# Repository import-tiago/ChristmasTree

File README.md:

# ChristmasTree

## PCB Preview

## Schematic

## Bill of Materials
| Qty | Parts | Description | Value | Package |
|--|--|--|--|--|
1|R1|SMD Resistor|10k ±5%|R0603
2|R2/R3|SMD Resistor|22R ±5%|R0603
1|R4|SMD Resistor|150R ±5%|R0603
1|R5|SMD Resistor|220k ±5%|R0603
1|C1|SMD Capacitor|1uF / 50V|C0805
1|C2|SMD Capacitor|10nF / 50V|C0603
2|C3/C5|SMD Capacitor|1uF / 50V|C0603
17|C4/C6~C21|SMD Capacitor|100nF / 50V|C0603
1|LDR1|PTH LDR|1 MΩ (Lux 0) / 10-20 KΩ (Lux 10)|5mm
1|Y1|SMD Crystal|8MHz|5.0mm x 3.2mm
1|U1|SMD Integrated Circuit|RT9193-33GB|SOT23-5
1|U2|SMD Integrated Circuit|ATMEGA32U4|QFN-44
2|D1/D2|SMD Diode|SS34|DO214AB
1|CN1|SMD Connector|MISB-SW-5B|Micro USB Type B
1|CN2|PTH Connector|JST-PH-2P|2-pin
13|LED1~LED13|SMD RGB LED|WS2812B|5050

### Contributing
0. Give this project a :star:
1. Create an issue and describe your idea.
2. [Fork it](https://github.com/import-tiago/ChristmasTree/fork).
3. Create your feature branch (`git checkout -b my-new-feature`).
4. Commit your changes (`git commit -a -m "Added feature title"`).
5. Publish the branch (`git push origin my-new-feature`).
6. Create a new pull request.
7. Done! :heavy_check_mark:

### License Information
<br /><span xmlns:dct="http://purl.org/dc/terms/" property="dct:title">ChristmasTree</span> by <a xmlns:cc="http://creativecommons.org/ns#" href="https://github.com/import-tiago" property="cc:attributionName" rel="cc:attributionURL">Tiago Silva</a> is licensed under a <a rel="license" href="http://creativecommons.org/licenses/by-sa/4.0/">Creative Commons Attribution-ShareAlike 4.0 International License</a>.<br />Permissions beyond the scope of this license may be available at <a xmlns:cc="http://creativecommons.org/ns#" href="https://twitter.com/import_tiago" rel="cc:morePermissions">tiagodepaulasilva@gmail.com</a>.

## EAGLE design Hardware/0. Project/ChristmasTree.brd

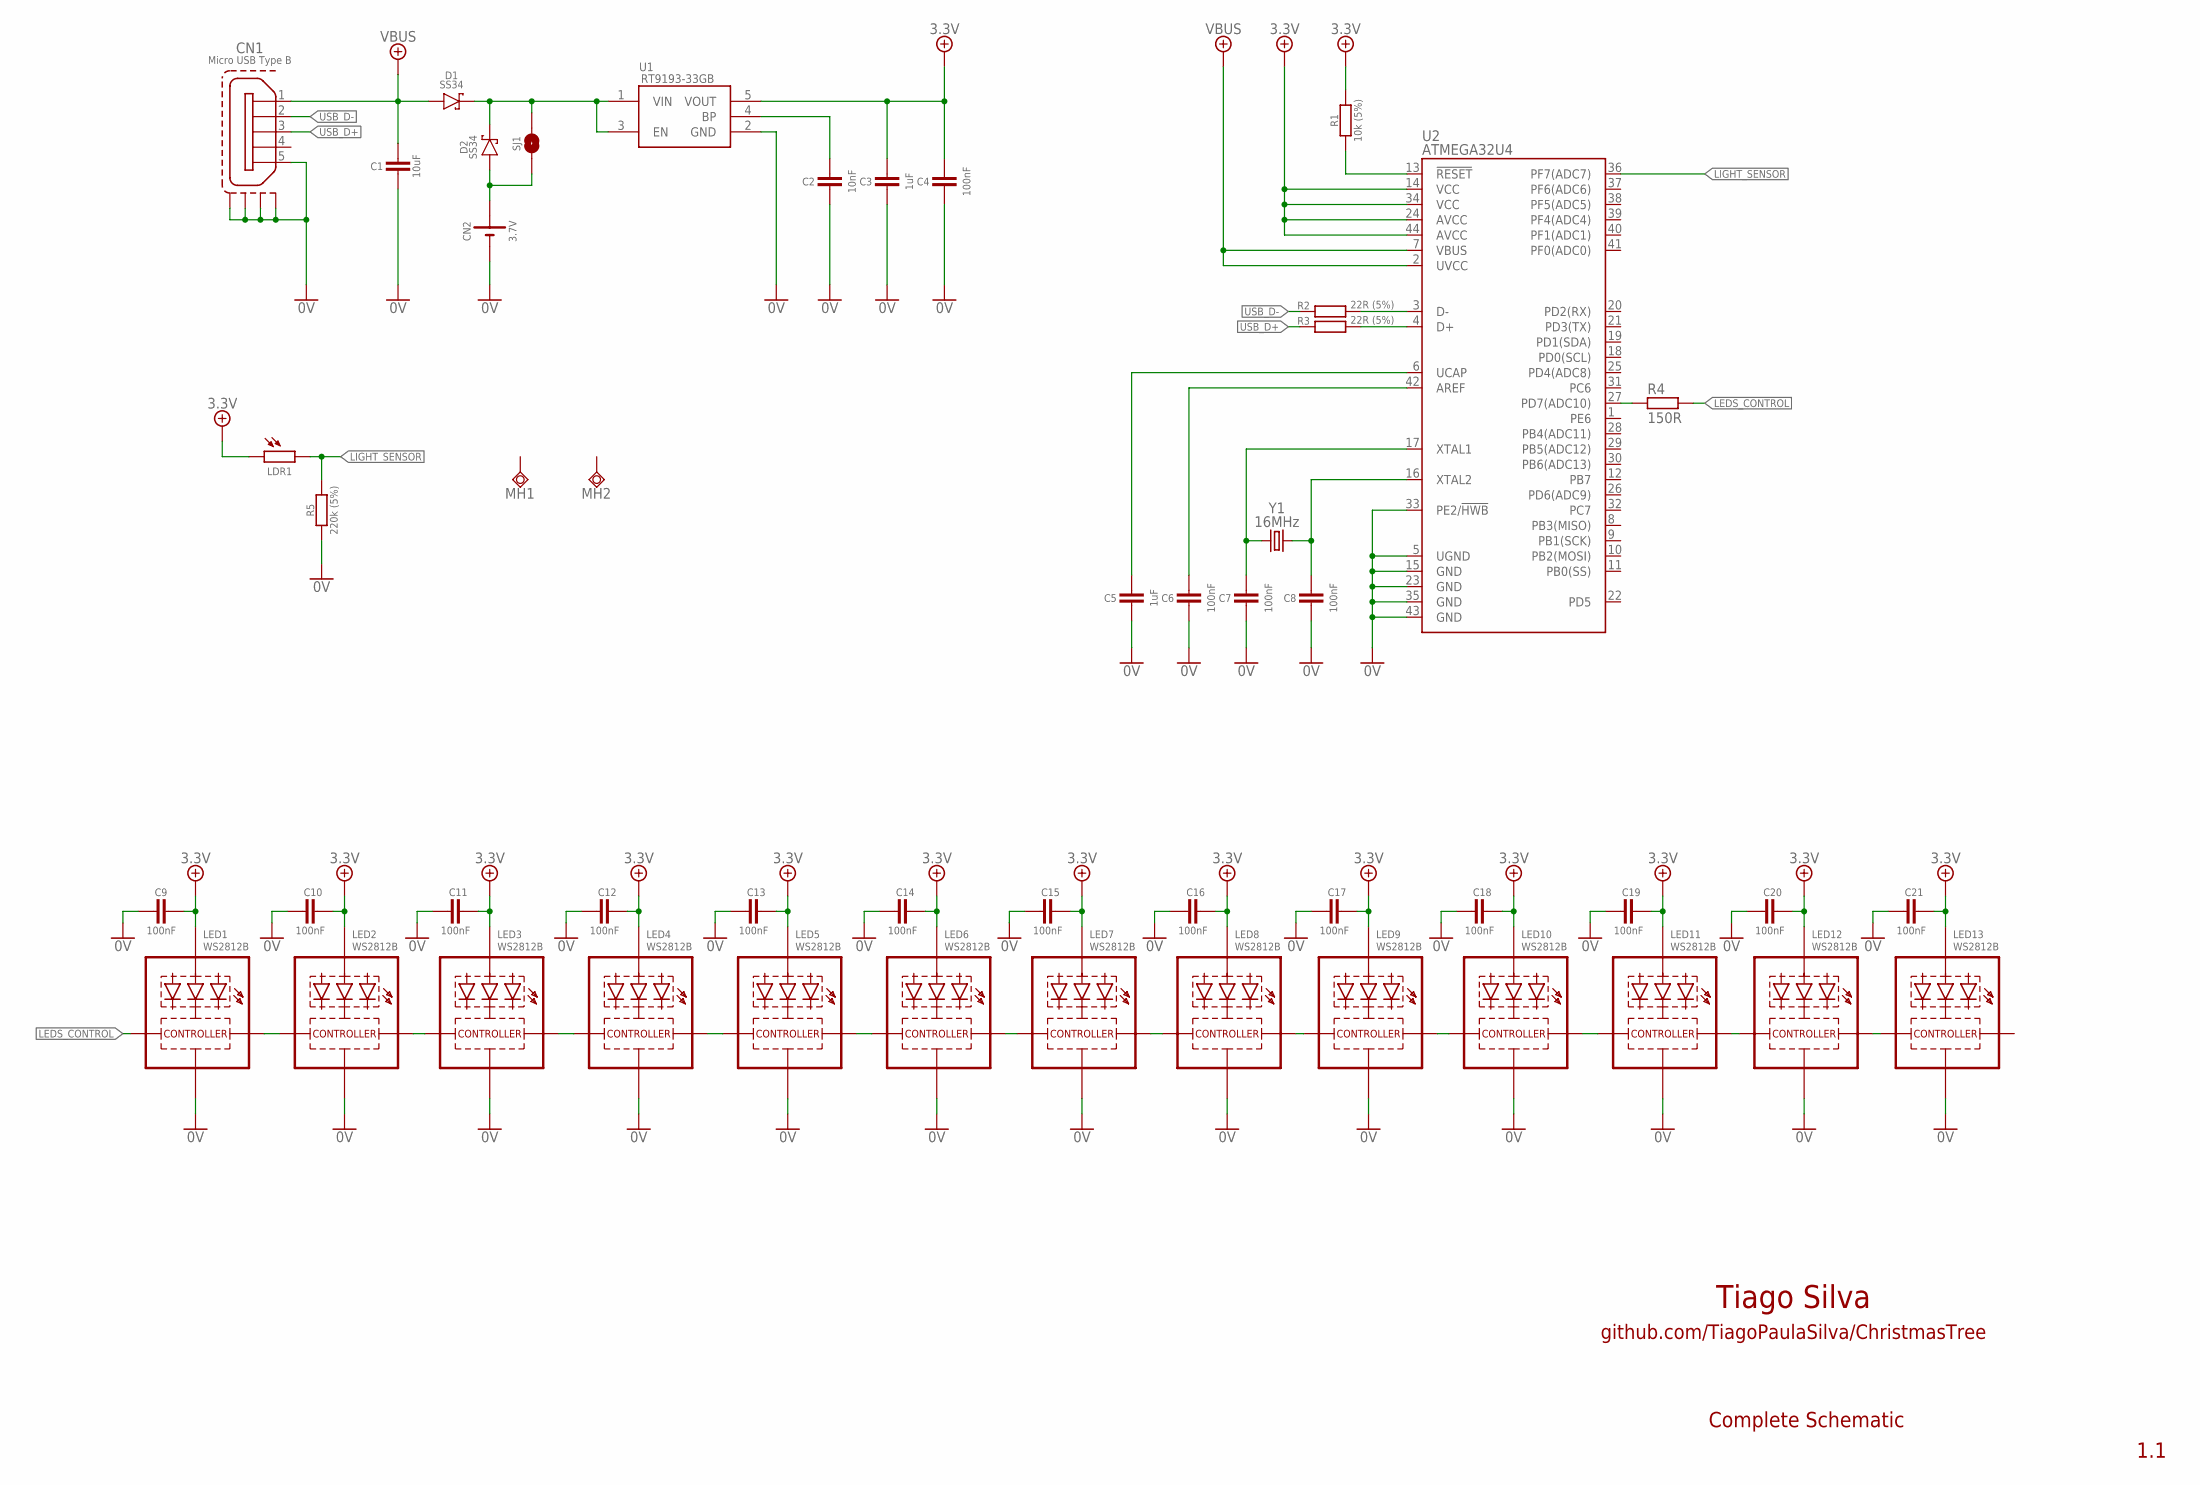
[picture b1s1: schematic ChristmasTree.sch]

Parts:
C1: 10uF; C0805
C2: 10nF; C0603
C3, C5: 1uF; C0603
C4, C6, C7, C8, C9, C10, C11, C12, C13, C14, C15, C16, C17, C18, C19, C20, C21: 100nF; C0603
CN1: Micro USB Type B; 10118193-0001LF
CN2: 3.7V; JST-PH2
D1, D2: SS34; DO214AB
LDR1: A1050_09; T0-46-A10XX
LED1, LED2, LED3, LED4, LED5, LED6, LED7, LED8, LED9, LED10, LED11, LED12, LED13: WS2812B; 5050
MH1, MH2: TPSQTP20R; TP20R
R1: 10k (5%); R0603
R2, R3: 22R (5%); R0603
R4: 150R; R0603
R5: 220k (5%); R0603
SJ1: SJ
U1: RT9193-33GB; SOT94P279X129-5N
U2: ATMEGA32U4; TESTING_QFN-44
Y1: 16MHz; 5.0X3.2_KX-9A

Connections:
0V: C1.2, C2.2, C3.2, C4.2, C5.2, C6.2, C7.2, C8.2, C9.2, C10.2, C11.2, C12.2, C13.2, C14.2, C15.2, C16.2, C17.2, C18.2, C19.2, C20.2, C21.2, CN1.5, CN1.MP1 (S1), CN1.MP2 (S2), CN1.MP3 (S3), CN1.MP4 (S4), CN2.2 (-), LED1.3-GND (GND), LED2.3-GND (GND), LED3.3-GND (GND), LED4.3-GND (GND), LED5.3-GND (GND), LED6.3-GND (GND), LED7.3-GND (GND), LED8.3-GND (GND), LED9.3-GND (GND), LED10.3-GND (GND), LED11.3-GND (GND), LED12.3-GND (GND), LED13.3-GND (GND), R5.1, U1.2 (GND), U2.5 (UGND), U2.15 (GND), U2.23 (GND), U2.33 (PE2/!HWB), U2.35 (GND), U2.43 (GND)
3.3V: C3.1, C4.1, C9.1, C10.1, C11.1, C12.1, C13.1, C14.1, C15.1, C16.1, C17.1, C18.1, C19.1, C20.1, C21.1, LDR1.1, LED1.1-VDD (VDD), LED2.1-VDD (VDD), LED3.1-VDD (VDD), LED4.1-VDD (VDD), LED5.1-VDD (VDD), LED6.1-VDD (VDD), LED7.1-VDD (VDD), LED8.1-VDD (VDD), LED9.1-VDD (VDD), LED10.1-VDD (VDD), LED11.1-VDD (VDD), LED12.1-VDD (VDD), LED13.1-VDD (VDD), R1.2, U1.5 (VOUT), U2.14 (VCC), U2.24 (AVCC), U2.34 (VCC), U2.44 (AVCC)
LEDS_CONTROL: LED1.4-DIN (DI), R4.2
LIGHT_SENSOR: LDR1.2, R5.2, U2.36 (PF7(ADC7))
unnamed: LED3.2-DOUT (DO), LED4.4-DIN (DI)
unnamed: LED1.2-DOUT (DO), LED2.4-DIN (DI)
unnamed: R4.1, U2.27 (PD7(ADC10))
unnamed: LED2.2-DOUT (DO), LED3.4-DIN (DI)
unnamed: LED5.2-DOUT (DO), LED6.4-DIN (DI)
unnamed: LED8.2-DOUT (DO), LED9.4-DIN (DI)
unnamed: LED6.2-DOUT (DO), LED7.4-DIN (DI)
unnamed: LED10.2-DOUT (DO), LED11.4-DIN (DI)
unnamed: LED9.2-DOUT (DO), LED10.4-DIN (DI)
unnamed: LED12.2-DOUT (DO), LED13.4-DIN (DI)
unnamed: LED4.2-DOUT (DO), LED5.4-DIN (DI)
unnamed: R3.2, U2.4 (D+)
unnamed: LED11.2-DOUT (DO), LED12.4-DIN (DI)
unnamed: LED7.2-DOUT (DO), LED8.4-DIN (DI)
unnamed: C7.1, U2.17 (XTAL1), Y1.1
unnamed: C8.1, U2.16 (XTAL2), Y1.3 (2)
unnamed: C5.1, U2.6 (UCAP)
unnamed: C6.1, U2.42 (AREF)
unnamed: CN2.1 (+), D2.A, SJ1.1
unnamed: R2.2, U2.3 (D-)
unnamed: C2.1, U1.4 (BP)
RESET: R1.1, U2.13 (!RESET)
USB_D+: CN1.3, R3.1
USB_D-: CN1.2, R2.1
VBAT: D1.C (K), D2.C (K), SJ1.2, U1.1 (VIN), U1.3 (EN)
VBUS: C1.1, CN1.1, D1.A, U2.2 (UVCC), U2.7 (VBUS)

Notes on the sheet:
Tiago Silva
github.com/TiagoPaulaSilva/ChristmasTree
1.1
Complete Schematic

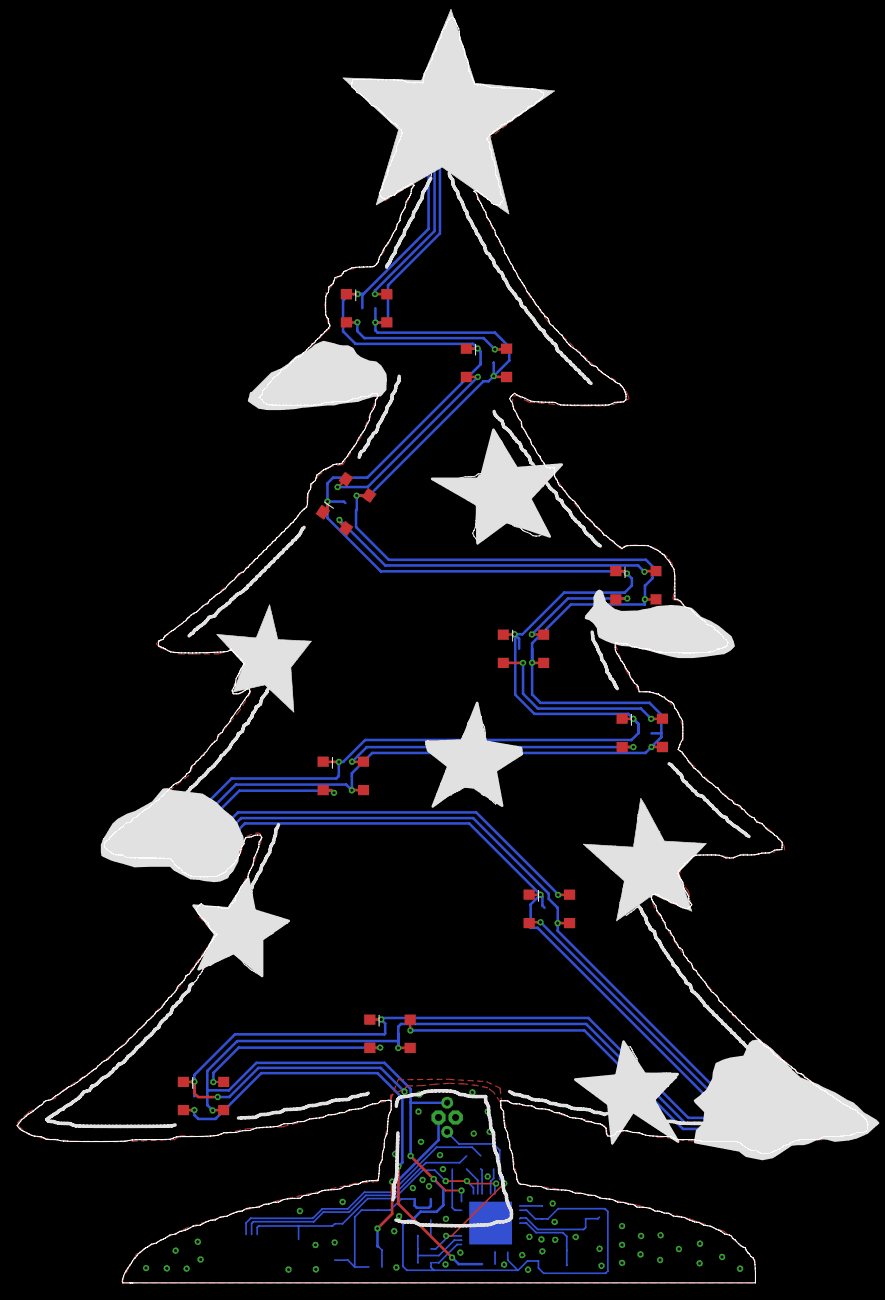
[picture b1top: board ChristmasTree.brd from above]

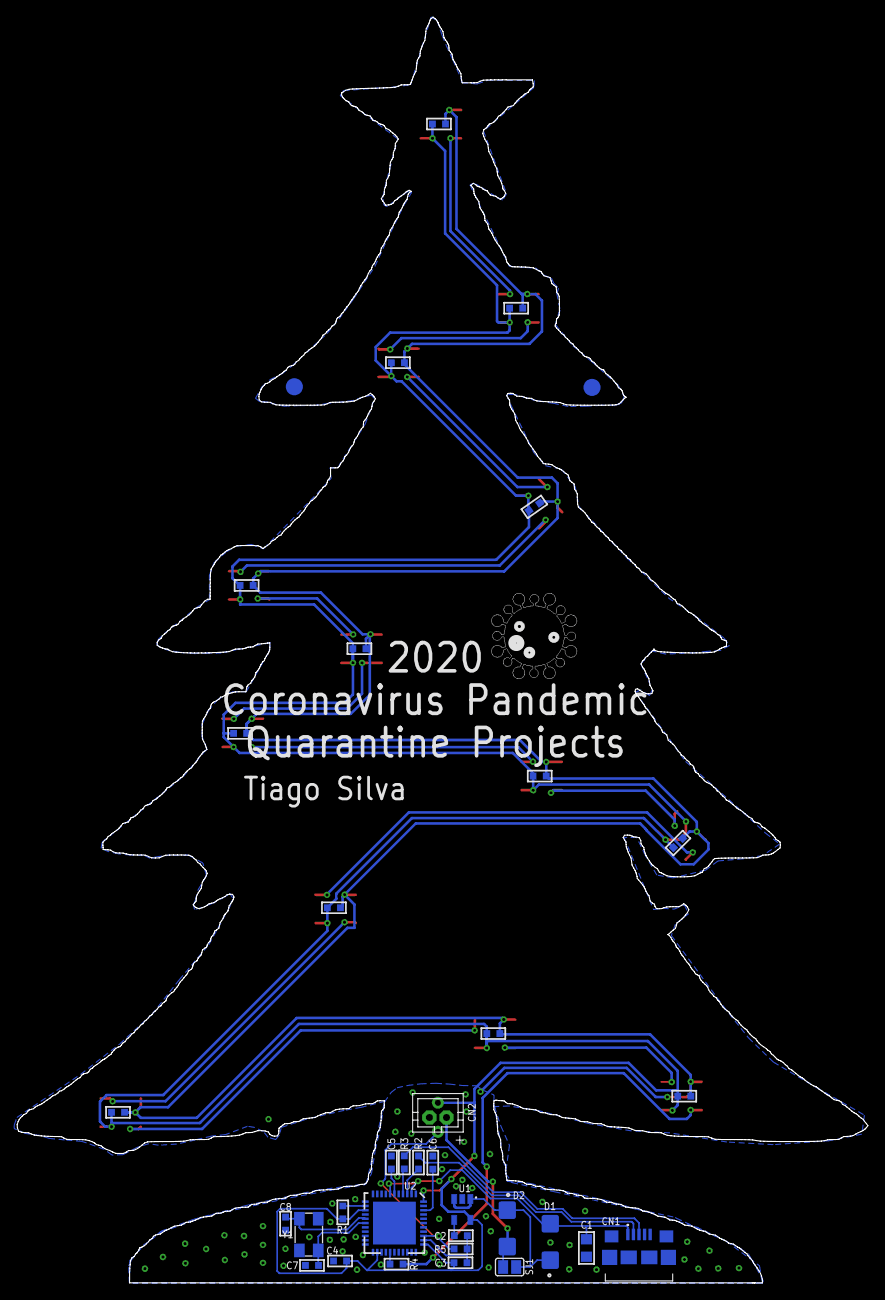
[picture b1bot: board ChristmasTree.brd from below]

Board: 2 copper layers, 99.3 x 147.7 mm, 50 parts (37 on the bottom side), 30 nets.

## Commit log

2020-09-25 PCB 100mm
2020-09-27 PCB 1.0 done
2020-09-27 .gitattributes added
2020-10-11 BoM added
2020-10-11 New datasheets added
2020-10-16 Basic firmware test
2020-10-17 Light sensor code and LEDs effects working
2020-10-17 New light level trigger
2020-10-17 Adequacy of values in some components
2020-10-17 Schematic preview updated to v1.1
2020-10-17 BOM updated to 1.1 schematic version
2020-10-17 .gitattributes removed
2023-07-21 usernames in URLs updated

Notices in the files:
parts and their libraries:
My-RLC: Copyright (C) 2007, Bob Starr
crystal-geyer_V1_0: Copyright: Geyer-Electronic
